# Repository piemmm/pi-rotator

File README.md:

# pi-rotator
The GS-232 costs far too much, so here's a simple Pi based antenna rotator which uses through-hole components wherever possible

The project is CC-BY-SA 

This project is currently still EXPERIMENTAL until the board design is finalised, and the driver software made more useful.

Getting Started:

pirotator is installed in the default user home directory - you can change this if you want.

Create the pirotator directory and change into it:

````
mkdir /home/pi/pirotator
cd /home/pi/pirotator
````

extract the contents of the repository folder ./home/pirotator to /home/pi/pirotator (this contains config.xml, start.sh, etc)

Then, make start.sh executable (if it is not already):

````
chmod u+x start.sh
````

install java 8 (java11+ support available once pi4j is updated):
 
````
sudo apt install openjdk-8-jdk
````

Copy the pirotator.service to systemd (only if you want to start at boot):

````
sudo cp pirotator.service /etc/systemd/system/pirotator.service
````

Then, enable the service

````
sudo systemctl enable pirotator.service
````

After that you should be good to go and can type:

````
sudo service pirotator.service start
````

To enable PPS + GPS + NTPd so you can have your own stratum one equivalent server:

Install the relevant bits:

````
sudo apt install gpsd gpsd-clients python-gi-cairo pps-tools ntp
````

Add this to /boot/config.txt

````
dtoverlay=pps-gpio,gpiopin=4,capture_clear
````

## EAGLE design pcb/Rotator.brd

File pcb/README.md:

The PCB files are created with Eagle PCB and the design is CC-BY-SA.

This is still experimental.

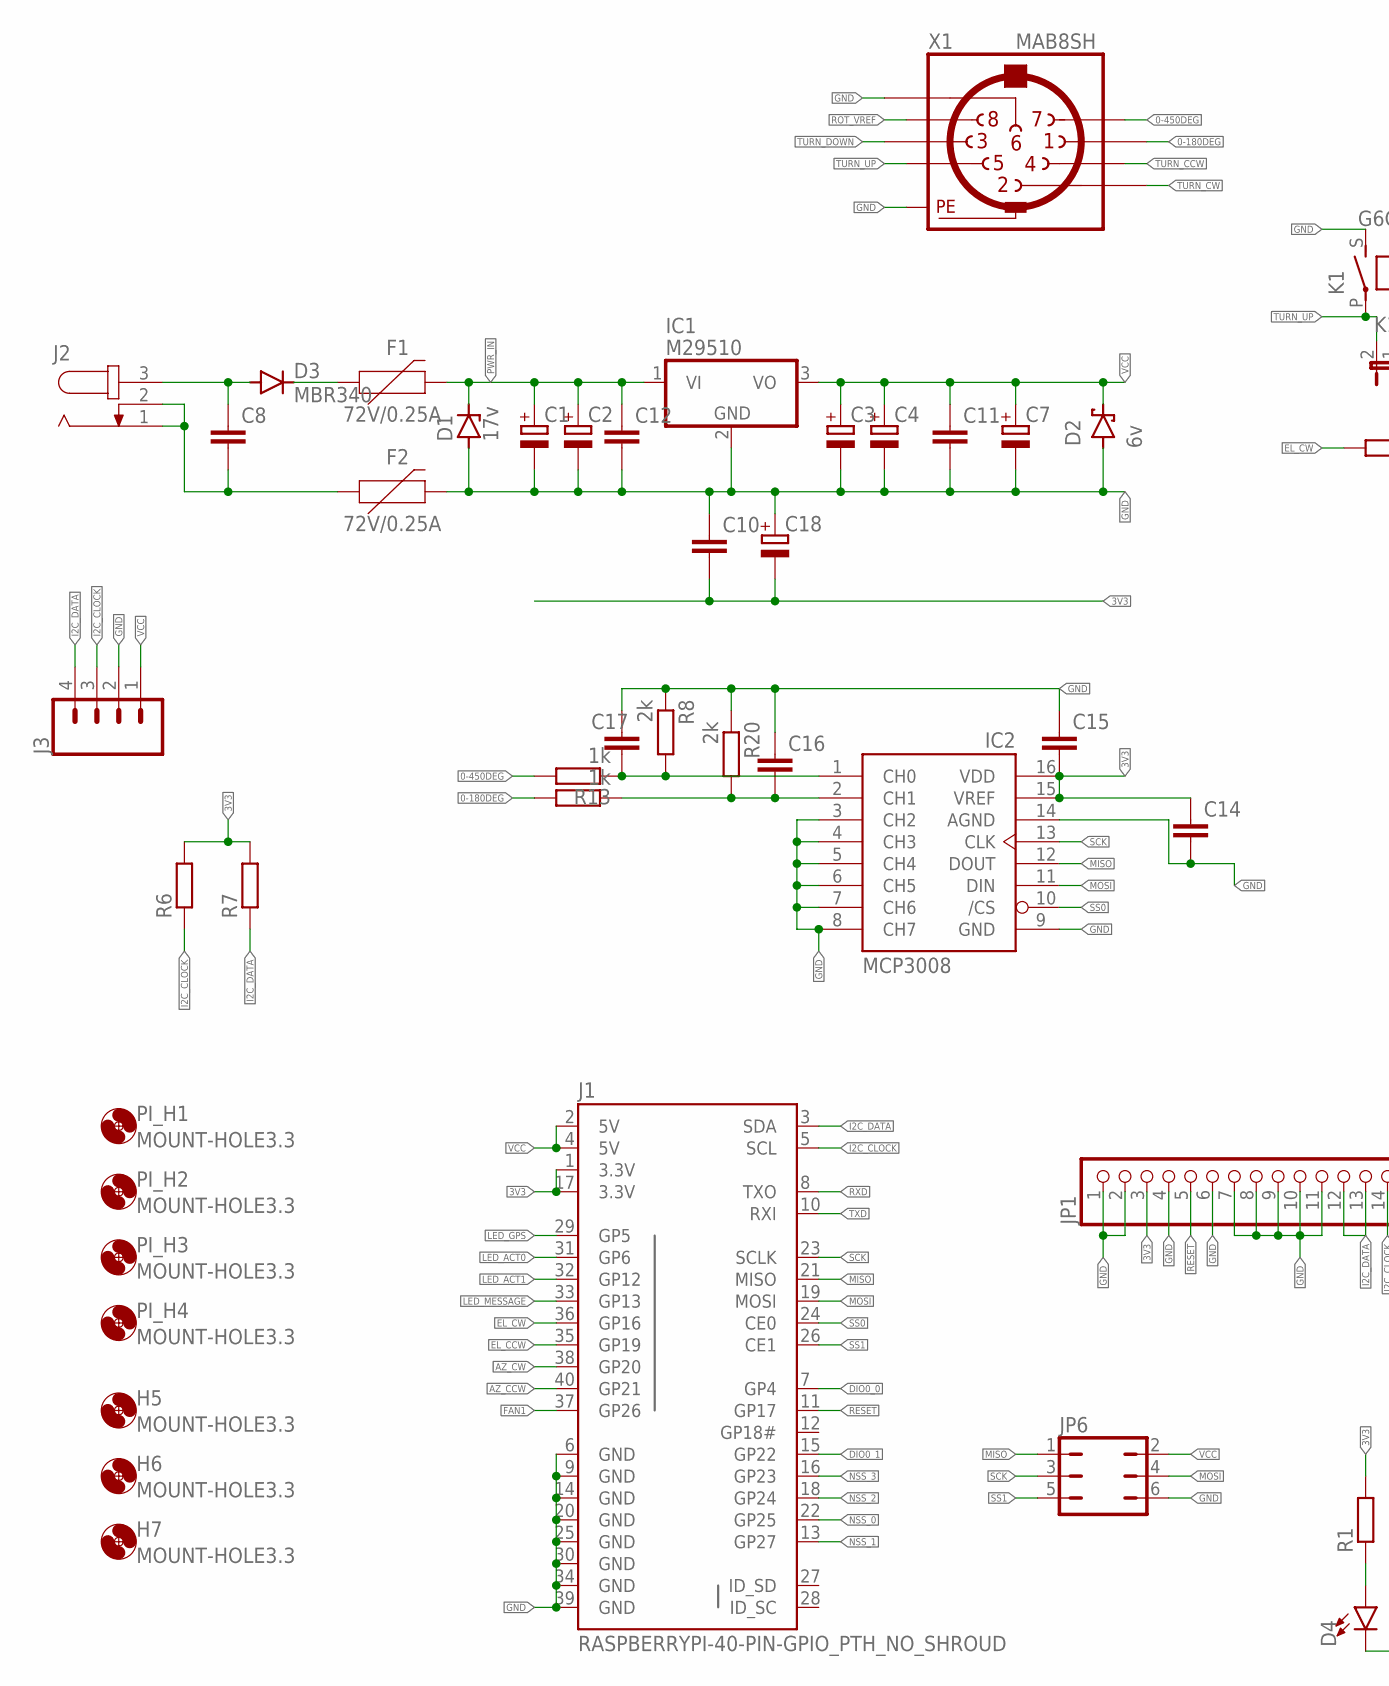
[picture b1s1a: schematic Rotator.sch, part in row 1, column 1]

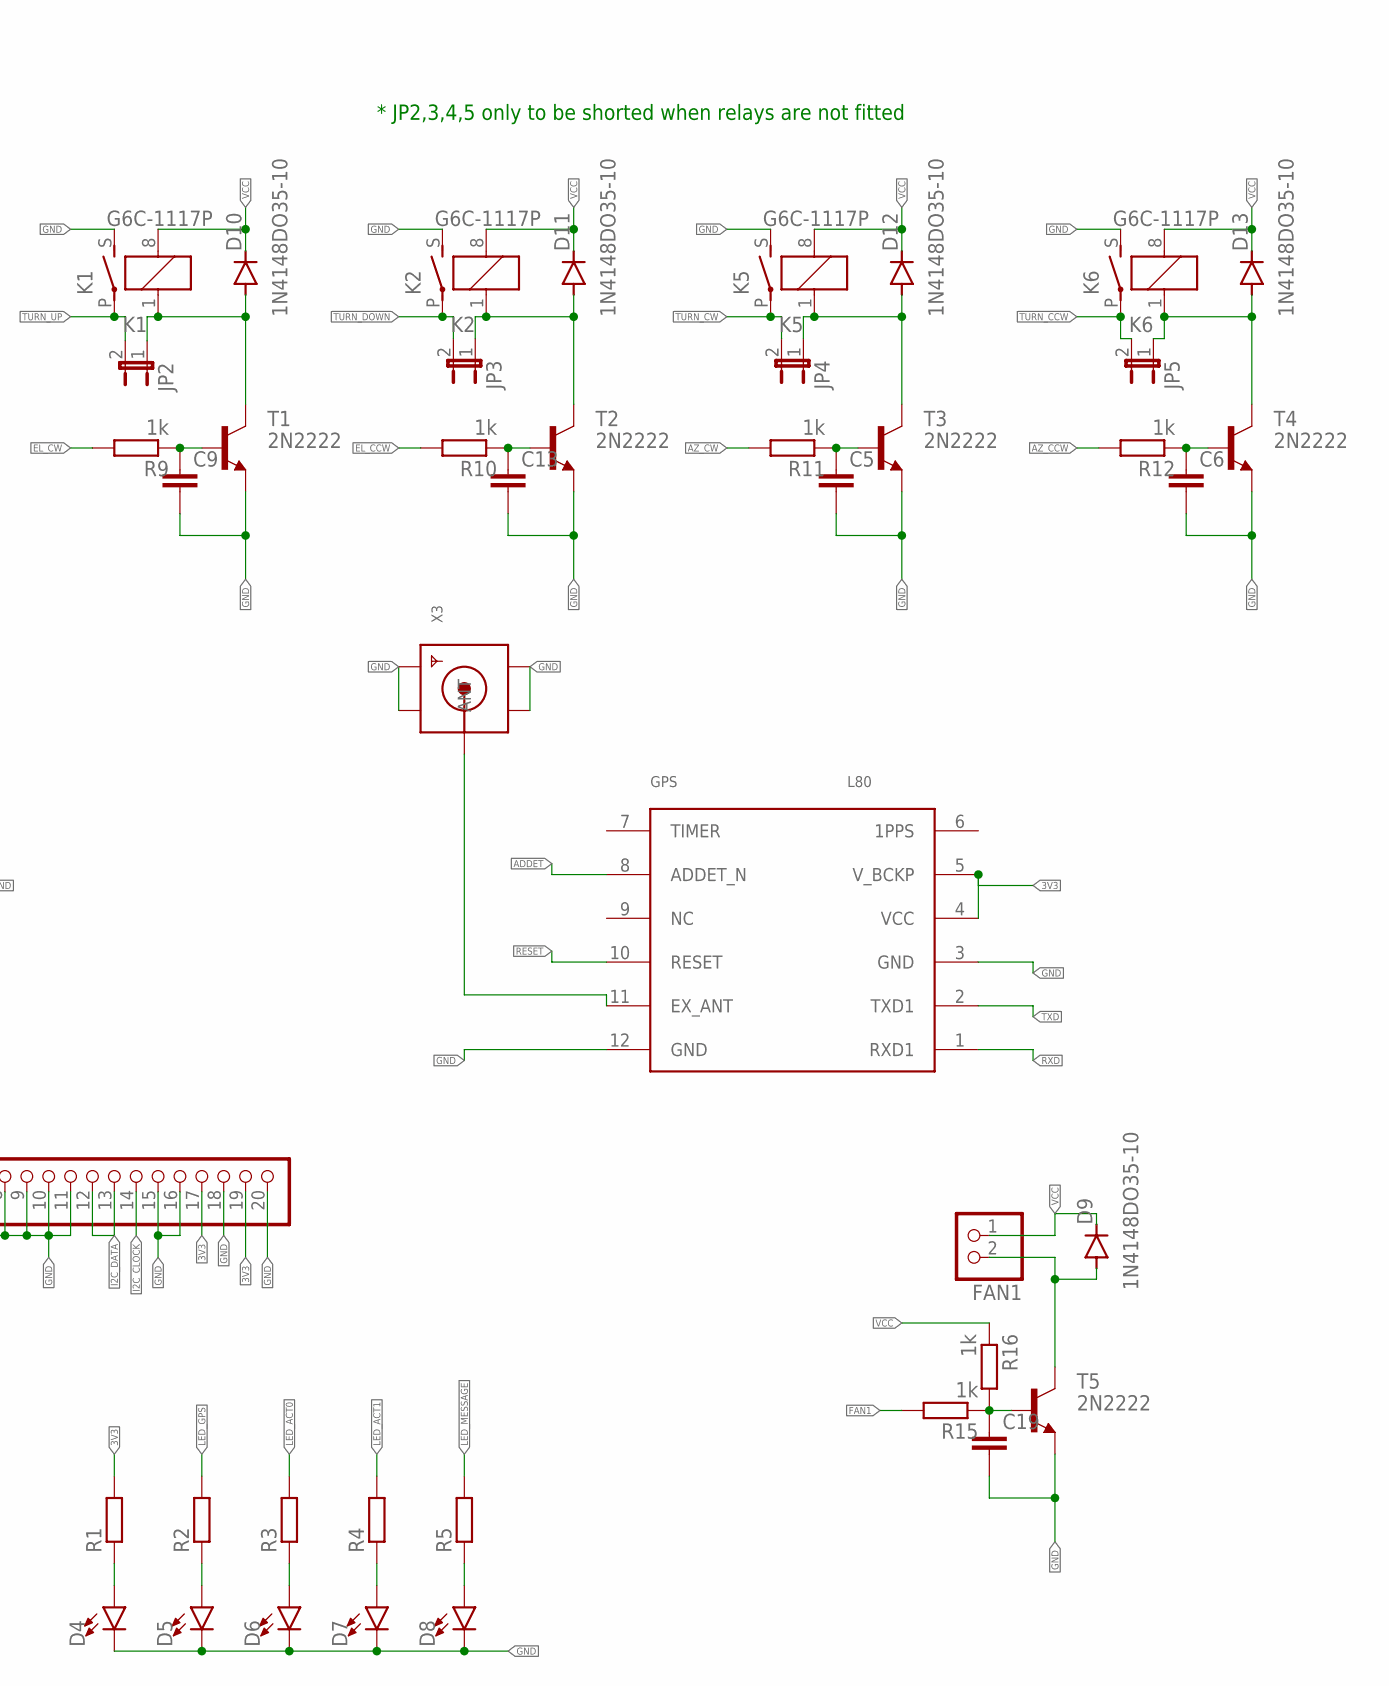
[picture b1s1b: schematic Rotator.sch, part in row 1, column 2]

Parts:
C1, C2: CPOL-EUE5-8.5; E5-8,5
C3, C4, C7, C18: CPOL-EUE2.5-7; E2,5-7
C5, C6, C8, C9, C10, C11, C12, C13, C14, C15, C16, C17, C19: C-EU050-025X075; C050-025X075
D1: 17v; F126Z12
D2: 6v; F126Z12
D3: MBR340; DO201-15
D4, D5, D6, D7, D8: LED3MM; LED_3MM
D9, D10, D11, D12, D13: 1N4148DO35-10; DO35-10
F1, F2: 72V/0.25A; PTH
FAN1: JST_2PIN-THM; JST-PH-2-THM
GPS: L80
H5, H6, H7: MOUNT-HOLE3.3; 3,3
IC1: M29510; TO220H
IC2: MCP3008; DIL16
J1: RASPBERRYPI-40-PIN-GPIO_PTH_NO_SHROUD; 2X20
J2: JACK-PLUG0; SPC4077
J3: CONN_04; 1X04
JP1: PINHD-1X20; 1X20
JP2, JP3, JP4, JP5: JP1E; JP1
JP6: JP3Q
K1, K2, K5, K6: G6C-1117P
PI_H1, PI_H2, PI_H3, PI_H4: MOUNT-HOLE3.3; 3,3
R1, R2, R3, R4, R5, R6, R7: R-EU_0207/10; 0207/10
R8, R20: 2k; 0207/10
R9, R10, R11, R12, R13, R14, R15, R16: 1k; 0207/10
T1, T2, T3, T4, T5: 2N2222; TO92-EBC-OVAL
X1: MAB8SH
X3: SMACONNECTOR_EDGE; SMA_EDGELAUNCH

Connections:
0-180DEG: R14.2, X1.1
0-450DEG: R13.2, X1.7
3V3: C10.2, C14.1, C15.2, C18.-, GPS.4 (VCC), GPS.5 (V_BCKP), IC2.15 (VREF), IC2.16 (VDD), J1.1 (3.3V), J1.17 (3.3V), JP1.3, JP1.17, JP1.19, R1.2, R6.2, R7.2
ADDET: GPS.8 (ADDET_N)
AZ_CCW: J1.40 (GP21), R12.2
AZ_CW: J1.38 (GP20), R11.2
DIO0_0: J1.7 (GP4)
DIO0_1: J1.15 (GP22)
EL_CCW: J1.35 (GP19), R10.2
EL_CW: J1.36 (GP16), R9.2
FAN1: J1.37 (GP26), R15.2
FANHDR-: D9.A, FAN1.2 (1), T5.C
GND: C1.-, C2.-, C3.-, C4.-, C5.2, C6.2, C7.-, C9.2, C10.1, C11.2, C12.2, C13.2, C14.2, C15.1, C16.1, C17.1, C18.+, C19.2, D1.A, D2.A, D4.K (C), D5.K (C), D6.K (C), D7.K (C), D8.K (C), F2.P$2 (2), GPS.3 (GND), GPS.12 (GND), IC1.2 (GND), IC2.3 (CH2), IC2.4 (CH3), IC2.5 (CH4), IC2.6 (CH5), IC2.7 (CH6), IC2.8 (CH7), IC2.9 (GND), IC2.14 (AGND), J1.6 (GND), J1.9 (GND), J1.14 (GND), J1.20 (GND), J1.25 (GND), J1.30 (GND), J1.34 (GND), J1.39 (GND), J3.2, JP1.1, JP1.2, JP1.4, JP1.6, JP1.7, JP1.8, JP1.9, JP1.10, JP1.11, JP1.15, JP1.16, JP1.18, JP1.20, JP6.6, K1.S, K2.S, K5.S, K6.S, R8.1, R20.1, T1.E, T2.E, T3.E, T4.E, T5.E, X1.6, X1.PE, X1.PE@ (PE), X3.GND@1 (GND4), X3.GND@2 (GND3), X3.GND@3 (GND2), X3.GND@4 (GND1)
I2C_CLOCK: J1.5 (SCL), J3.3, JP1.14, R6.1
I2C_DATA: J1.3 (SDA), J3.4, JP1.12, JP1.13, R7.1
LED_ACT0: J1.31 (GP6), R3.2
LED_ACT1: J1.32 (GP12), R4.2
LED_GPS: J1.29 (GP5), R2.2
LED_MESSAGE: J1.33 (GP13), R5.2
MISO: IC2.12 (DOUT), J1.21 (MISO), JP6.1
MOSI: IC2.11 (DIN), J1.19 (MOSI), JP6.4
unnamed: C5.1, R11.1, T3.B
unnamed: D12.A, JP4.1, K5.1, T3.C
unnamed: C8.1, D3.A, J2.3
unnamed: C8.2, F2.P$1 (1), J2.1, J2.2
unnamed: GPS.11 (EX_ANT), X3.P (ANT)
unnamed: C13.1, R10.1, T2.B
unnamed: D3.C, F1.P$1 (1)
unnamed: C6.1, R12.1, T4.B
unnamed: C19.1, R15.1, R16.2, T5.B
unnamed: D13.A, JP5.1, K6.1, T4.C
unnamed: D4.A, R1.1
unnamed: D5.A, R2.1
unnamed: D6.A, R3.1
unnamed: D7.A, R4.1
unnamed: D8.A, R5.1
unnamed: C9.1, R9.1, T1.B
unnamed: D10.A, JP2.1, K1.1, T1.C
unnamed: D11.A, JP3.1, K2.1, T2.C
unnamed: C17.2, IC2.1 (CH0), R8.2, R13.1
unnamed: C16.2, IC2.2 (CH1), R14.1, R20.2
NSS_0: J1.22 (GP25)
NSS_1: J1.13 (GP27)
NSS_2: J1.18 (GP24)
NSS_3: J1.16 (GP23)
PWR_IN: C1.+, C2.+, C12.1, D1.C, F1.P$2 (2), IC1.1 (VI)
RESET: GPS.10 (RESET), J1.11 (GP17), JP1.5
ROT_VREF: X1.8
RXD: GPS.1 (RXD1), J1.8 (TXO)
SCK: IC2.13 (CLK), J1.23 (SCLK), JP6.3
SS0: IC2.10 (/CS), J1.24 (CE0)
SS1: J1.26 (CE1), JP6.5
TURN_CCW: JP5.2, K6.P, X1.4
TURN_CW: JP4.2, K5.P, X1.2
TURN_DOWN: JP3.2, K2.P, X1.3
TURN_UP: JP2.2, K1.P, X1.5
TXD: GPS.2 (TXD1), J1.10 (RXI)
VCC: C3.+, C4.+, C7.+, C11.1, D2.C, D9.C, D10.C, D11.C, D12.C, D13.C, FAN1.1 (2), IC1.3 (VO), J1.2 (5V), J1.4 (5V), J3.1, JP6.2, K1.8 (2), K2.8 (2), K5.8 (2), K6.8 (2), R16.1

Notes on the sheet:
* JP2,3,4,5 only to be shorted when relays are not fitted

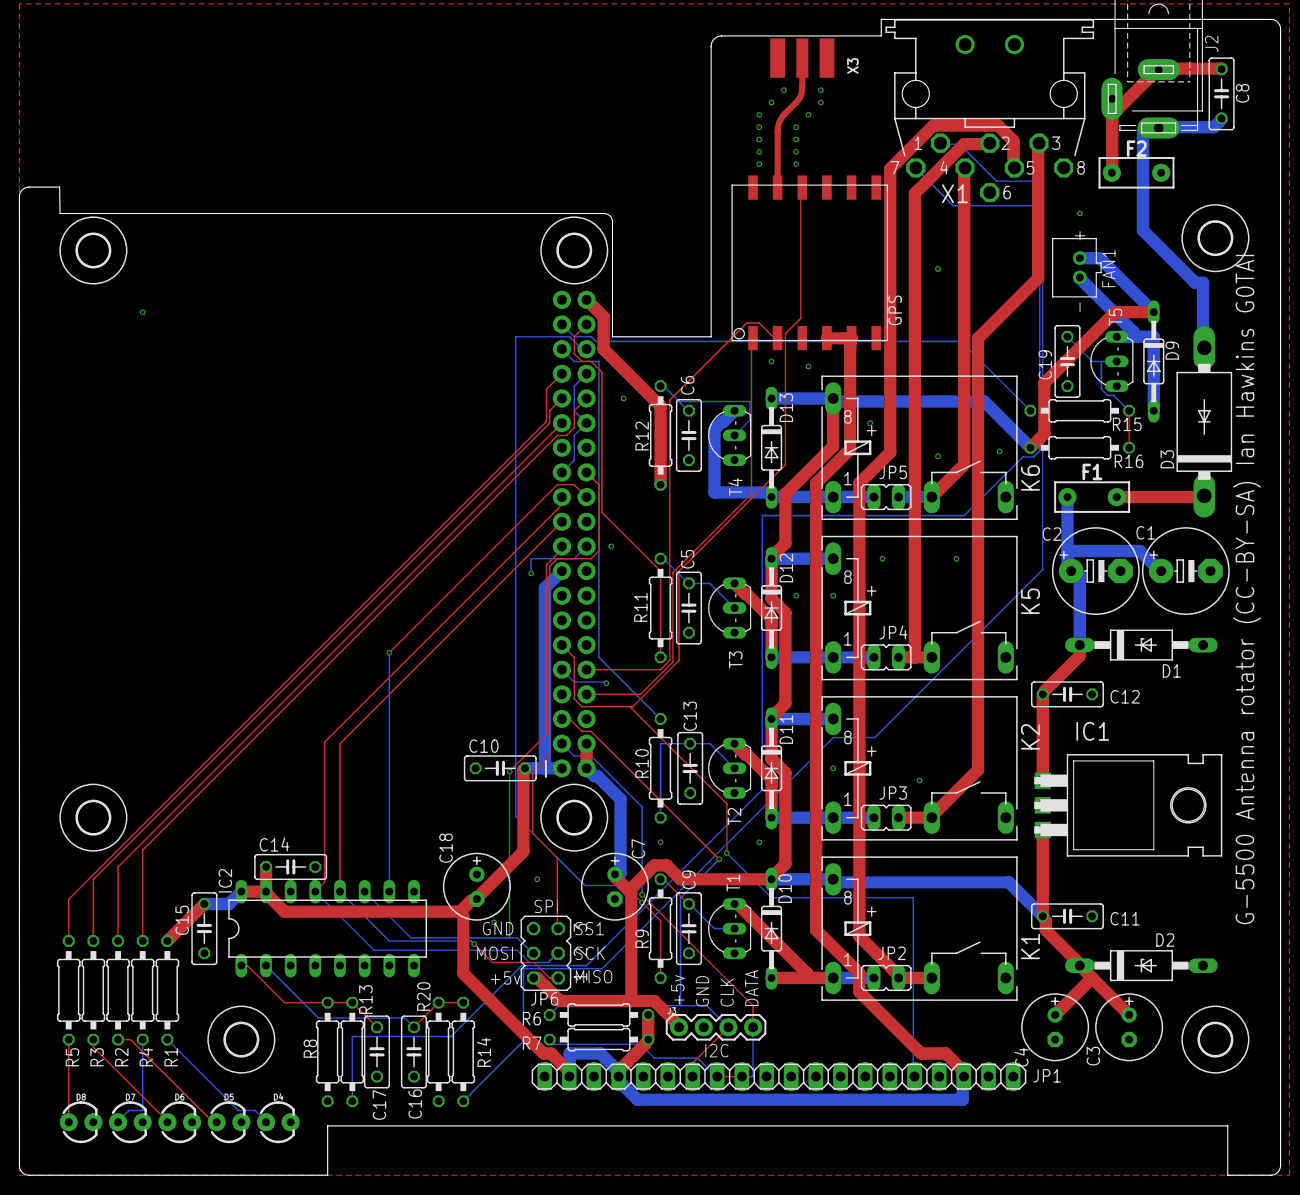
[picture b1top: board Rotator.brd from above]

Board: 2 copper layers, 129.9 x 119.0 mm, 82 parts (1 on the bottom side), 50 nets.

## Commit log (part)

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2020-07-21 Initial project creation
2020-07-25 Basics mostly done waiting on new PCB.
2020-07-30 Rotator internals create
2020-08-03 Basic rotator done. Macdoppler and rotctld basic support added
2020-08-03 Refactor code out of the ADC class into a more appropriate location
2020-08-06 Refactor, config.xml added, thermal monitor added
2020-08-06 Add missing files
2020-08-06 Refactor, GPS support added, APIs now configurable
2020-08-06 Initial PCB designs
2020-08-06 Fix config xml and tidy up rotctld compatible controller a little
2020-08-06 Bugfixes, config update, doc image added
2020-08-06 Doc updates
2020-08-06 Add readme for pcbs
2020-08-06 Add cc-by-sa message
2020-08-06 Moving led now works correctly.
2020-08-06 Add some instructions, create a basic service for systemd.
2020-08-06 Add parking+timeout support
2020-08-06 Attempt to show the fault light if the jvm exits.
2021-03-31 Bump guava from 28.2-jre to 29.0-jre
    Bumps [guava](https://github.com/google/guava) from 28.2-jre to 29.0-jre.
    - [Release notes](https://github.com/google/guava/releases)
    - [Commits](https://github.com/google/guava/commits)
2021-06-21 Update pom.xml
    bump guava
2021-09-22 Remove unneeded dio pins, add workaround for bug in nmea parser library, add constraints for mcp3008 a/d readings for noisy pots.
2023-01-21 Add files via upload
    Rotator PCB
2023-06-14 Bump guava from 30.0-jre to 32.0.0-jre
    Bumps [guava](https://github.com/google/guava) from 30.0-jre to 32.0.0-jre.
    - [Release notes](https://github.com/google/guava/releases)
    - [Commits](https://github.com/google/guava/commits)
    ---
    updated-dependencies:
    - dependency-name: com.google.guava:guava
2025-05-28 Bump commons-beanutils:commons-beanutils from 1.9.4 to 1.11.0
    Bumps commons-beanutils:commons-beanutils from 1.9.4 to 1.11.0.
    ---
    updated-dependencies:
    - dependency-name: commons-beanutils:commons-beanutils
    dependency-version: 1.11.0
    dependency-type: direct:production

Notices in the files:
pcb/Rotator.brd:
G-5500 Antenna rotator (CC-BY-SA) Ian Hawkins G0TAI
parts and their libraries:
SparkFun-Connectors: Licensing: Creative Commons ShareAlike 4.0 International - https://creativecommons.org/licenses/by-sa/4.0
